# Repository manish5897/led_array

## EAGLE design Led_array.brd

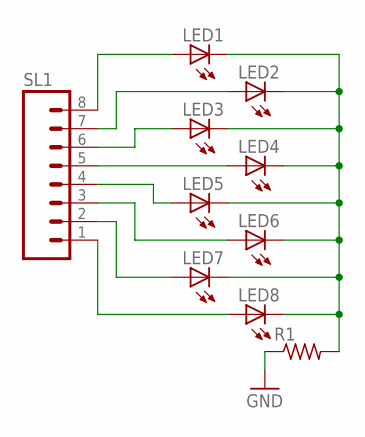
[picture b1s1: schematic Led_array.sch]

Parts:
LED1, LED2, LED3, LED4, LED5, LED6, LED7, LED8: LED3MM
R1: R-US_0204/7; 0204/7
SL1: M08; 08P

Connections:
GND: R1.1
unnamed: LED1.A, SL1.8
unnamed: LED2.A, SL1.7
unnamed: LED1.K (C), LED2.K (C), LED3.K (C), LED4.K (C), LED5.K (C), LED6.K (C), LED7.K (C), LED8.K (C), R1.2
unnamed: LED3.A, SL1.6
unnamed: LED4.A, SL1.5
unnamed: LED5.A, SL1.4
unnamed: LED6.A, SL1.3
unnamed: LED7.A, SL1.2
unnamed: LED8.A, SL1.1

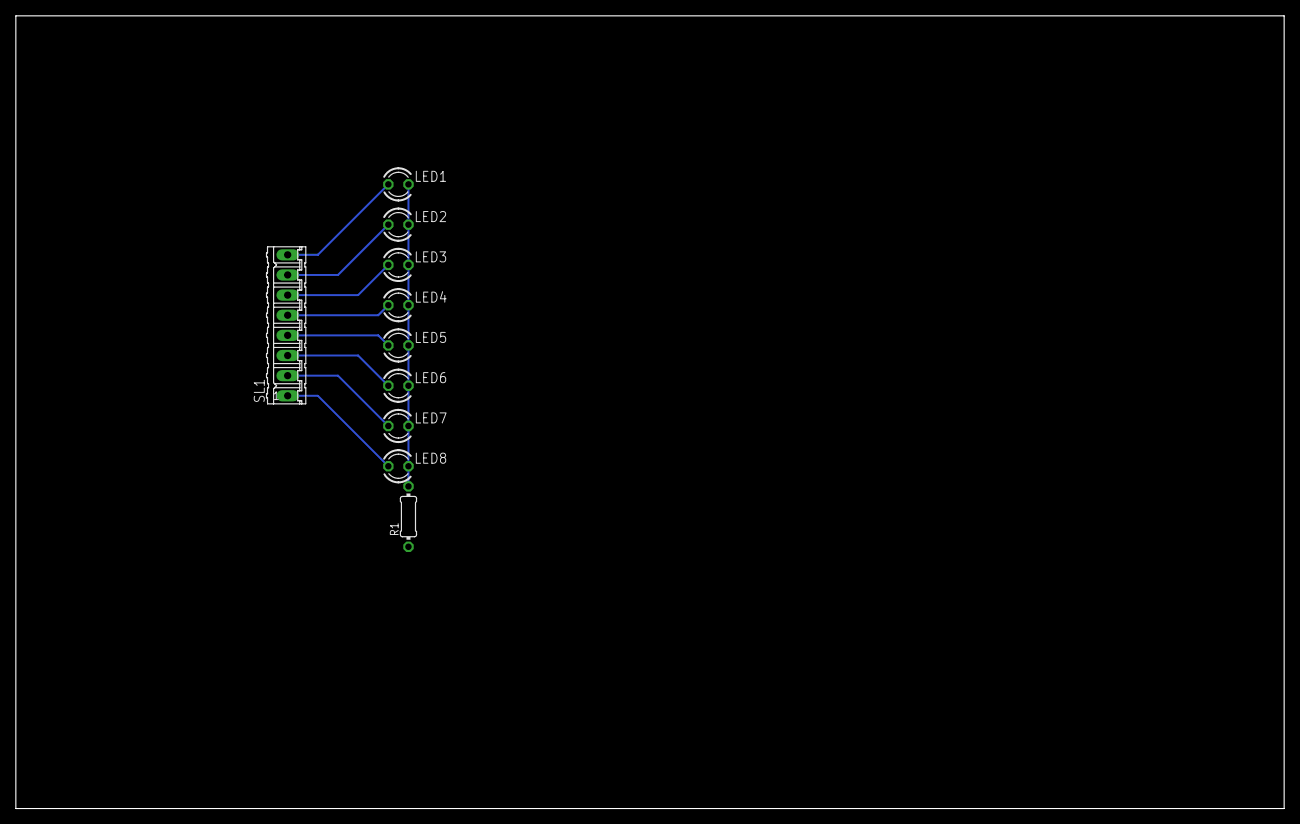
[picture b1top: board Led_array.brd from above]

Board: 2 copper layers, 160.0 x 100.0 mm, 10 parts (0 on the bottom side), 9 nets.

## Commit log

2018-08-13 array of led
